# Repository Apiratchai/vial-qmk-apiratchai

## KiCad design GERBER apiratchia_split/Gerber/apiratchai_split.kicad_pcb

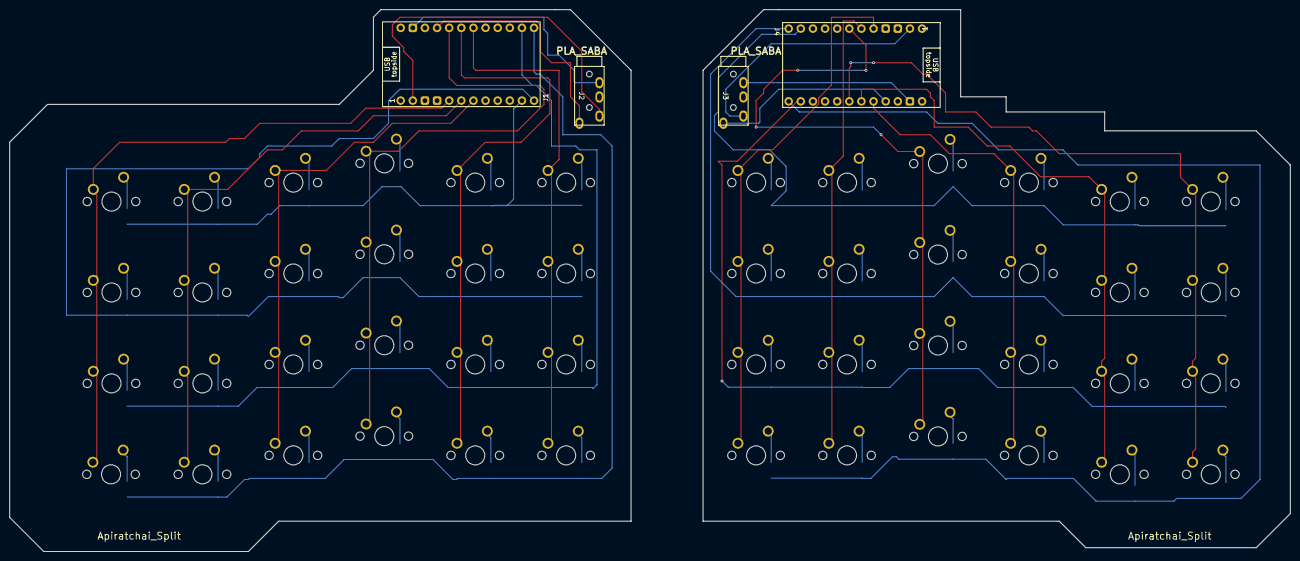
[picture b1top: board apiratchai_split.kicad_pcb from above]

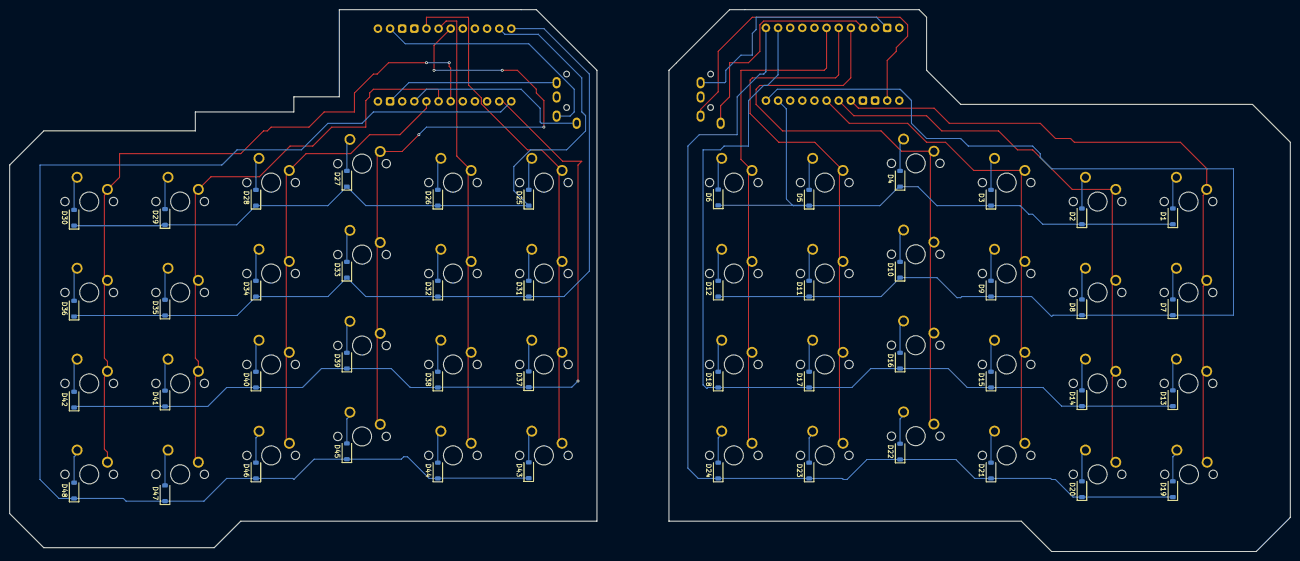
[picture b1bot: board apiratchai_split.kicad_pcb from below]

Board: 2 copper layers, 268.3 x 113.5 mm, 100 parts (48 on the bottom side), 74 nets.

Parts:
D1, D2, D3, D4, D5, D6, D7, D8, D9, D10, D11, D12, D13, D14, D15, D16, D17, D18, D19, D20, D21, D22, D23, D24, D25, D26, D27, D28, D29, D30, D31, D32, D33, D34, D35, D36, D37, D38, D39, D40, D41, D42, D43, D44, D45, D46, D47, D48: D_Small; D_SOD-123
J1, J4: Conn_02x12_Top_Bottom; ProMicro_USBup
J2, J3: AudioJack4; CON_MJ-4PP-9
MX1, MX2, MX3, MX4, MX5, MX6, MX7, MX8, MX9, MX10, MX11, MX12, MX13, MX14, MX15, MX16, MX17, MX18, MX19, MX20, MX21, MX22, MX23, MX24, MX25, MX26, MX27, MX28, MX29, MX30, MX31, MX32, MX33, MX34, MX35, MX36, MX37, MX38, MX39, MX40, MX41, MX42, MX43, MX44, MX45, MX46, MX47, MX48: MX_SW_solder; SW_MX_1u

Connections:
Col0: J1.5, MX1.1, MX7.1, MX13.1, MX19.1
Col0R: J4.5, MX25.1, MX31.1, MX37.1, MX43.1
Col1: J1.6, MX2.1, MX8.1, MX14.1, MX20.1
Col1R: J4.6, MX26.1, MX32.1, MX38.1, MX44.1
Col2: J1.7, MX3.1, MX9.1, MX15.1, MX21.1
Col2R: J4.7, MX27.1, MX33.1, MX39.1, MX45.1
Col3: J1.17, MX4.1, MX10.1, MX16.1, MX22.1
Col3R: J4.17, MX28.1, MX34.1, MX40.1, MX46.1
Col4: J1.18, MX5.1, MX11.1, MX17.1, MX23.1
Col4R: J4.18, MX29.1, MX35.1, MX41.1, MX47.1
Col5: J1.19, MX6.1, MX12.1, MX18.1, MX24.1
Col5R: J4.19, MX30.1, MX36.1, MX42.1, MX48.1
unnamed: D1.2 (A), MX1.2
unnamed: D2.2 (A), MX2.2
unnamed: D3.2 (A), MX3.2
unnamed: D4.2 (A), MX4.2
unnamed: D5.2 (A), MX5.2
unnamed: D6.2 (A), MX6.2
unnamed: D7.2 (A), MX7.2
unnamed: D8.2 (A), MX8.2
unnamed: D9.2 (A), MX9.2
unnamed: D10.2 (A), MX10.2
unnamed: D11.2 (A), MX11.2
unnamed: D12.2 (A), MX12.2
unnamed: D13.2 (A), MX13.2
unnamed: D14.2 (A), MX14.2
unnamed: D15.2 (A), MX15.2
unnamed: D16.2 (A), MX16.2
unnamed: D17.2 (A), MX17.2
unnamed: D18.2 (A), MX18.2
unnamed: D19.2 (A), MX19.2
unnamed: D20.2 (A), MX20.2
unnamed: D21.2 (A), MX21.2
unnamed: D22.2 (A), MX22.2
unnamed: D23.2 (A), MX23.2
unnamed: D24.2 (A), MX24.2
unnamed: D25.2 (A), MX25.2
unnamed: D26.2 (A), MX26.2
unnamed: D27.2 (A), MX27.2
unnamed: D28.2 (A), MX28.2
unnamed: D29.2 (A), MX29.2
unnamed: D30.2 (A), MX30.2
unnamed: D31.2 (A), MX31.2
unnamed: D32.2 (A), MX32.2
unnamed: D33.2 (A), MX33.2
unnamed: D34.2 (A), MX34.2
unnamed: D35.2 (A), MX35.2
unnamed: D36.2 (A), MX36.2
unnamed: D37.2 (A), MX37.2
unnamed: D38.2 (A), MX38.2
unnamed: D39.2 (A), MX39.2
unnamed: D40.2 (A), MX40.2
unnamed: D41.2 (A), MX41.2
unnamed: D42.2 (A), MX42.2
unnamed: D43.2 (A), MX43.2
unnamed: D44.2 (A), MX44.2
unnamed: D45.2 (A), MX45.2
unnamed: D46.2 (A), MX46.2
unnamed: D47.2 (A), MX47.2
unnamed: D48.2 (A), MX48.2
unnamed: J1.2, J2.R1
unnamed: J1.14, J2.S
unnamed: J1.16, J2.T
unnamed: J3.R1, J4.2
unnamed: J3.S, J4.14
unnamed: J3.T, J4.16
Row0: D1.1 (K), D2.1 (K), D3.1 (K), D4.1 (K), D5.1 (K), D6.1 (K), J1.11
Row0R: D25.1 (K), D26.1 (K), D27.1 (K), D28.1 (K), D29.1 (K), D30.1 (K), J4.11
Row1: D7.1 (K), D8.1 (K), D9.1 (K), D10.1 (K), D11.1 (K), D12.1 (K), J1.12
Row1R: D31.1 (K), D32.1 (K), D33.1 (K), D34.1 (K), D35.1 (K), D36.1 (K), J4.12
Row2: D13.1 (K), D14.1 (K), D15.1 (K), D16.1 (K), D17.1 (K), D18.1 (K), J1.23
Row2R: D37.1 (K), D38.1 (K), D39.1 (K), D40.1 (K), D41.1 (K), D42.1 (K), J4.23
Row3: D19.1 (K), D20.1 (K), D21.1 (K), D22.1 (K), D23.1 (K), D24.1 (K), J1.24
Row3R: D43.1 (K), D44.1 (K), D45.1 (K), D46.1 (K), D47.1 (K), D48.1 (K), J4.24

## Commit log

2024-04-30 apiratchai_split_firmware ver 0.0.1
2024-05-04 add pcb file
